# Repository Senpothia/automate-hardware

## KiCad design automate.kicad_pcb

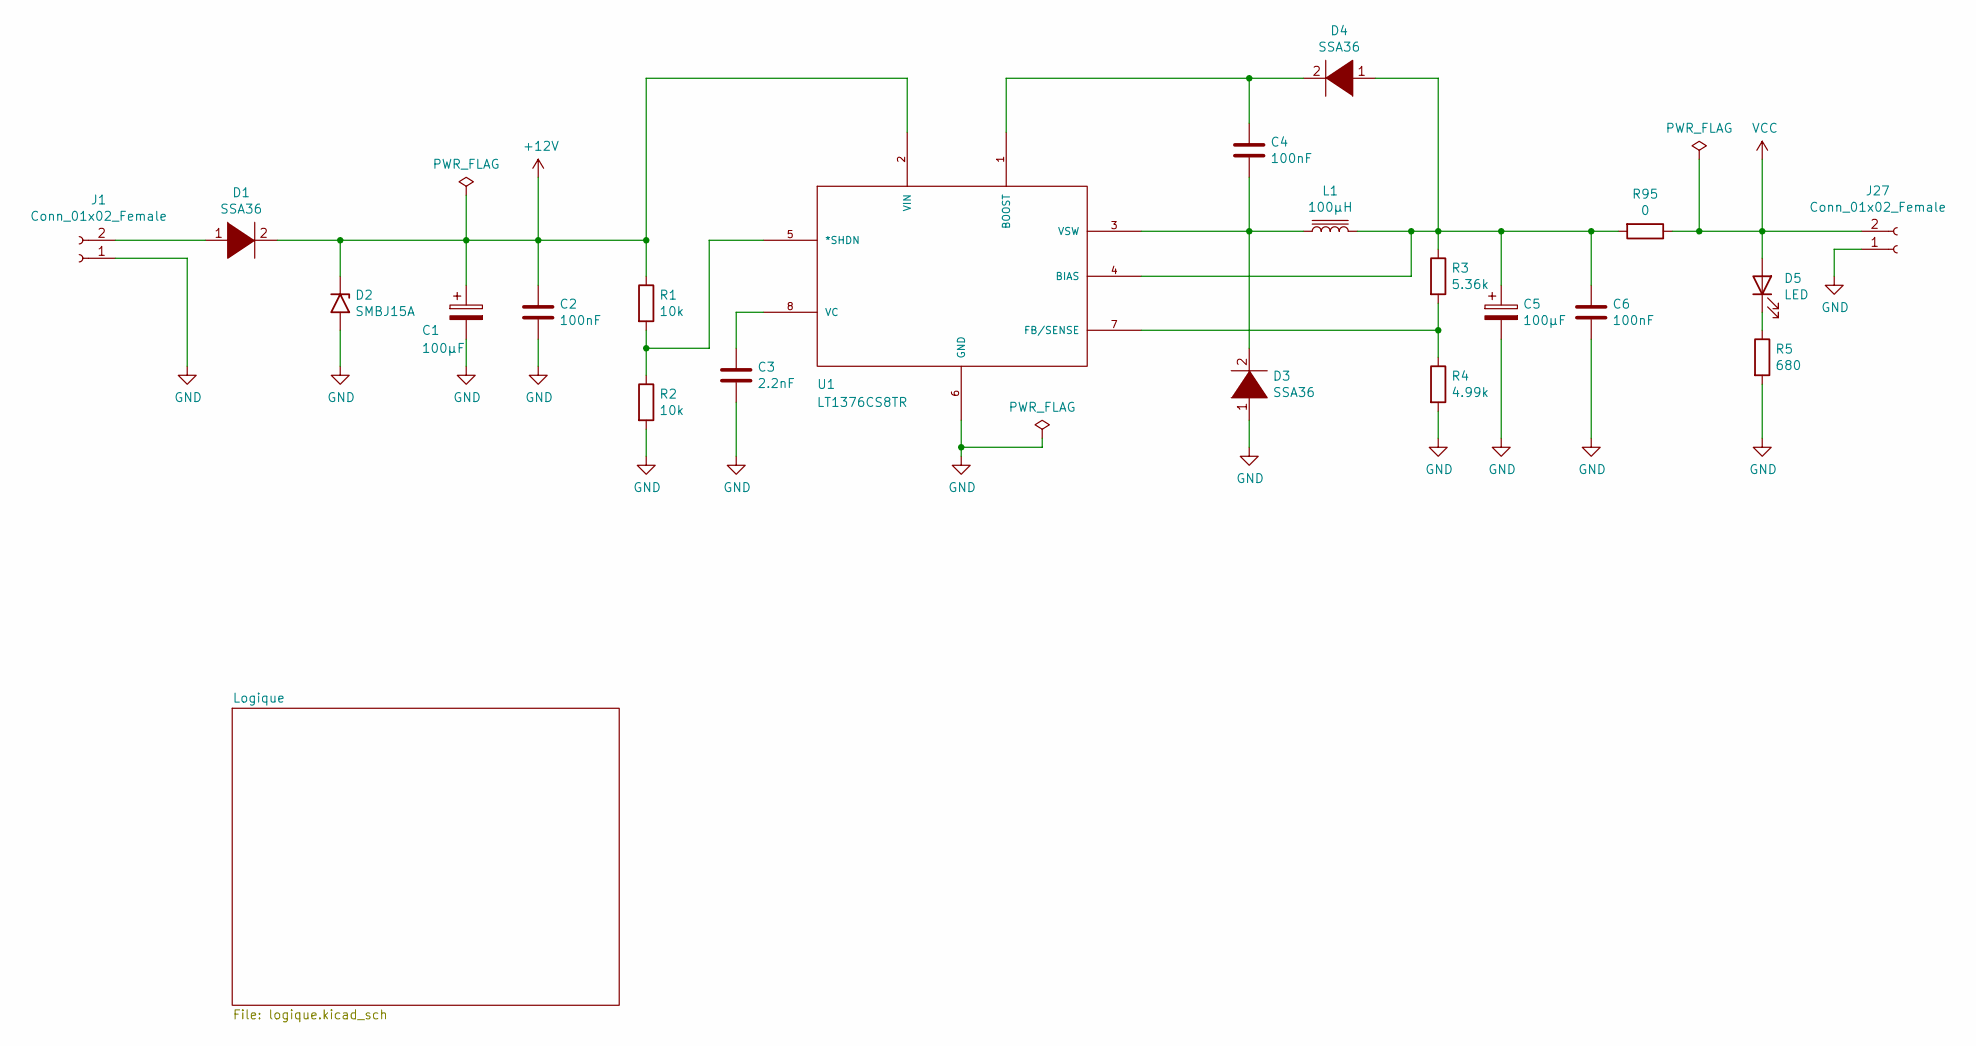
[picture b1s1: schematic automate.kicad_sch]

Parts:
C1, C5: 100µF; C_Elec_8x6.2
C2, C4, C6: 100nF; R_0805_2012Metric_Pad1.20x1.40mm_HandSolder
C3: 2.2nF; R_0805_2012Metric_Pad1.20x1.40mm_HandSolder
D1, D3, D4: SSA36; D_SMB_SSA36-Handsoldering
D2: SMBJ15A; D_SMB_Handsoldering
D5: LED; D_0805_2012Metric_Pad1.15x1.40mm_HandSolder
J1, J27: Conn_01x02_Female; conn-2pts-P5mm
L1: 100µH; L_Wuerth_WE-PD-Typ-LS-12x12
R1, R2: 10k; R_0805_2012Metric_Pad1.20x1.40mm_HandSolder
R3: 5.36k; R_0805_2012Metric_Pad1.20x1.40mm_HandSolder
R4: 4.99k; R_0805_2012Metric_Pad1.20x1.40mm_HandSolder
R5: 680; R_0805_2012Metric_Pad1.20x1.40mm_HandSolder
R95: 0; R_1206_3216Metric_Pad1.30x1.75mm_HandSolder
U1: LT1376CS8TR; SOIC-8_3.9x4.9mm_P1.27mm; MANUFACTURER_PART_NUMBER lt1376cs8#tr

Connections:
+12V: C1.1, C2.1, D1.2 (A), D2.1 (A1), R1.1, U1.2 (VIN); also elsewhere on the board
GND: C1.2, C2.2, C3.2, C5.2, C6.2, D2.2 (A2), D3.1 (K), J1.1, J27.1, R2.2, R4.2, R5.2, U1.6 (GND); also elsewhere on the board
unnamed: C3.1, U1.8 (VC)
unnamed: C4.1, D4.2 (A), U1.1 (BOOST)
unnamed: C4.2, D3.2 (A), L1.1, U1.3 (VSW)
unnamed: C5.1, C6.1, D4.1 (K), L1.2, R3.1, R95.2, U1.4 (BIAS)
unnamed: D1.1 (K), J1.2
unnamed: D5.1 (K), R5.1
unnamed: R1.2, R2.1, U1.5 (*SHDN)
unnamed: R3.2, R4.1, U1.7 (FB/SENSE)
VCC: D5.2 (A), J27.2, R95.1; also elsewhere on the board

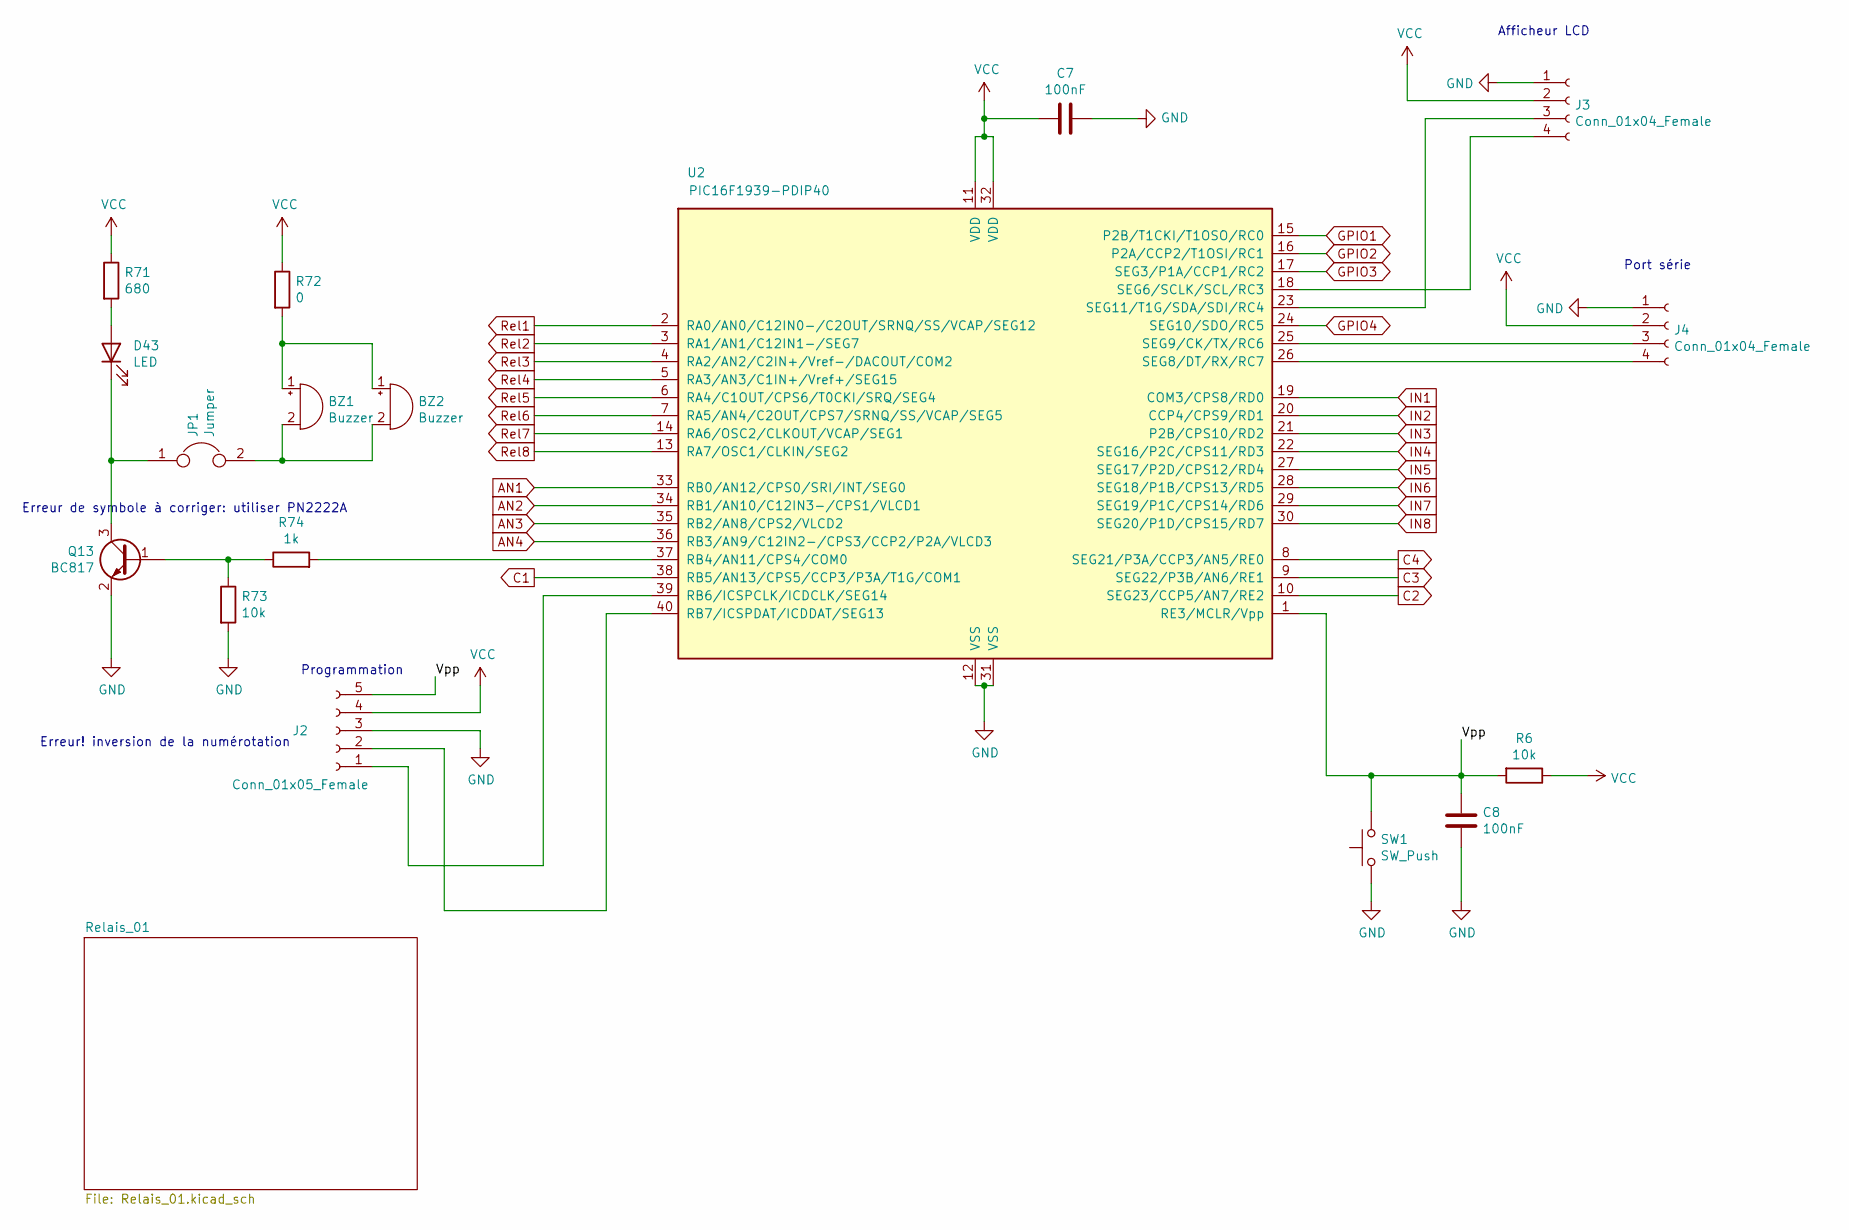
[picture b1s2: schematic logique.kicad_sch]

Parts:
BZ1: Buzzer; Buzzer_Mallory_AST1109MLTRQ
BZ2: Buzzer; Buzzer_12x9.5RM7.6
C7, C8: 100nF; R_0805_2012Metric_Pad1.20x1.40mm_HandSolder
D43: LED; LED_0805_2012Metric_Pad1.15x1.40mm_HandSolder
J2: Conn_01x05_Female; PinHeader_1x05_P2.54mm_Vertical
J3, J4: Conn_01x04_Female; conn-4pts-P5mm
JP1: Jumper; PinHeader_1x02_P2.54mm_Vertical
Q13: BC817; SOT-23.-BC817kicad_mod
R6, R73: 10k; R_0805_2012Metric_Pad1.20x1.40mm_HandSolder
R71: 680; R_0805_2012Metric_Pad1.20x1.40mm_HandSolder
R72: 0; R_0805_2012Metric_Pad1.20x1.40mm_HandSolder
R74: 1k; R_0805_2012Metric_Pad1.20x1.40mm_HandSolder
SW1: SW_Push; SW_PUSH_6mm_H5mm
U2: PIC16F1939-PDIP40; DIP-40_W15.24mm_LongPads

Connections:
/Logique/Vpp: C8.1, J2.5, R6.2, SW1.2, U2.1 (RE3/MCLR/Vpp)
AN1: U2.33 (RB0/AN12/CPS0/SRI/INT/SEG0); also elsewhere on the board
AN2: U2.34 (RB1/AN10/C12IN3-/CPS1/VLCD1); also elsewhere on the board
AN3: U2.35 (RB2/AN8/CPS2/VLCD2); also elsewhere on the board
AN4: U2.36 (RB3/AN9/C12IN2-/CPS3/CCP2/P2A/VLCD3); also elsewhere on the board
C1: U2.38 (RB5/AN13/CPS5/CCP3/P3A/T1G/COM1); also elsewhere on the board
C2: U2.10 (SEG23/CCP5/AN7/RE2); also elsewhere on the board
C3: U2.9 (SEG22/P3B/AN6/RE1); also elsewhere on the board
C4: U2.8 (SEG21/P3A/CCP3/AN5/RE0); also elsewhere on the board
GND: C7.1, C8.2, J2.3, J3.1, J4.1, Q13.2 (E), R73.2, SW1.1, U2.12 (VSS), U2.31 (VSS); also elsewhere on the board
GPIO1: U2.15 (P2B/T1CKI/T1OSO/RC0); also elsewhere on the board
GPIO2: U2.16 (P2A/CCP2/T1OSI/RC1); also elsewhere on the board
GPIO3: U2.17 (SEG3/P1A/CCP1/RC2); also elsewhere on the board
GPIO4: U2.24 (SEG10/SDO/RC5); also elsewhere on the board
IN1: U2.19 (COM3/CPS8/RD0); also elsewhere on the board
IN2: U2.20 (CCP4/CPS9/RD1); also elsewhere on the board
IN3: U2.21 (P2B/CPS10/RD2); also elsewhere on the board
IN4: U2.22 (SEG16/P2C/CPS11/RD3); also elsewhere on the board
IN5: U2.27 (SEG17/P2D/CPS12/RD4); also elsewhere on the board
IN6: U2.28 (SEG18/P1B/CPS13/RD5); also elsewhere on the board
IN7: U2.29 (SEG19/P1C/CPS14/RD6); also elsewhere on the board
IN8: U2.30 (SEG20/P1D/CPS15/RD7); also elsewhere on the board
unnamed: BZ1.1 (-), BZ2.1 (-), R72.2
unnamed: BZ1.2 (+), BZ2.2 (+), JP1.2
unnamed: D43.1 (K), JP1.1, Q13.3 (C)
unnamed: D43.2 (A), R71.2
unnamed: J2.1, U2.39 (RB6/ICSPCLK/ICDCLK/SEG14)
unnamed: J2.2, U2.40 (RB7/ICSPDAT/ICDDAT/SEG13)
unnamed: J3.3, U2.23 (SEG11/T1G/SDA/SDI/RC4)
unnamed: J3.4, U2.18 (SEG6/SCLK/SCL/RC3)
unnamed: J4.3, U2.25 (SEG9/CK/TX/RC6)
unnamed: J4.4, U2.26 (SEG8/DT/RX/RC7)
unnamed: Q13.1 (B), R73.1, R74.1
unnamed: R74.2, U2.37 (RB4/AN11/CPS4/COM0)
Rel1: U2.2 (RA0/AN0/C12IN0-/C2OUT/SRNQ/SS/VCAP/SEG12); also elsewhere on the board
Rel2: U2.3 (RA1/AN1/C12IN1-/SEG7); also elsewhere on the board
Rel3: U2.4 (RA2/AN2/C2IN+/Vref-/DACOUT/COM2); also elsewhere on the board
Rel4: U2.5 (RA3/AN3/C1IN+/Vref+/SEG15); also elsewhere on the board
Rel5: U2.6 (RA4/C1OUT/CPS6/T0CKI/SRQ/SEG4); also elsewhere on the board
Rel6: U2.7 (RA5/AN4/C2OUT/CPS7/SRNQ/SS/VCAP/SEG5); also elsewhere on the board
Rel7: U2.14 (RA6/OSC2/CLKOUT/VCAP/SEG1); also elsewhere on the board
Rel8: U2.13 (RA7/OSC1/CLKIN/SEG2); also elsewhere on the board
VCC: C7.2, J2.4, J3.2, J4.2, R6.1, R71.1, R72.1, U2.11 (VDD), U2.32 (VDD); also elsewhere on the board

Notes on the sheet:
Erreur! inversion de la numérotation
Afficheur LCD
Port série
Programmation
Erreur de symbole à corriger: utiliser PN2222A

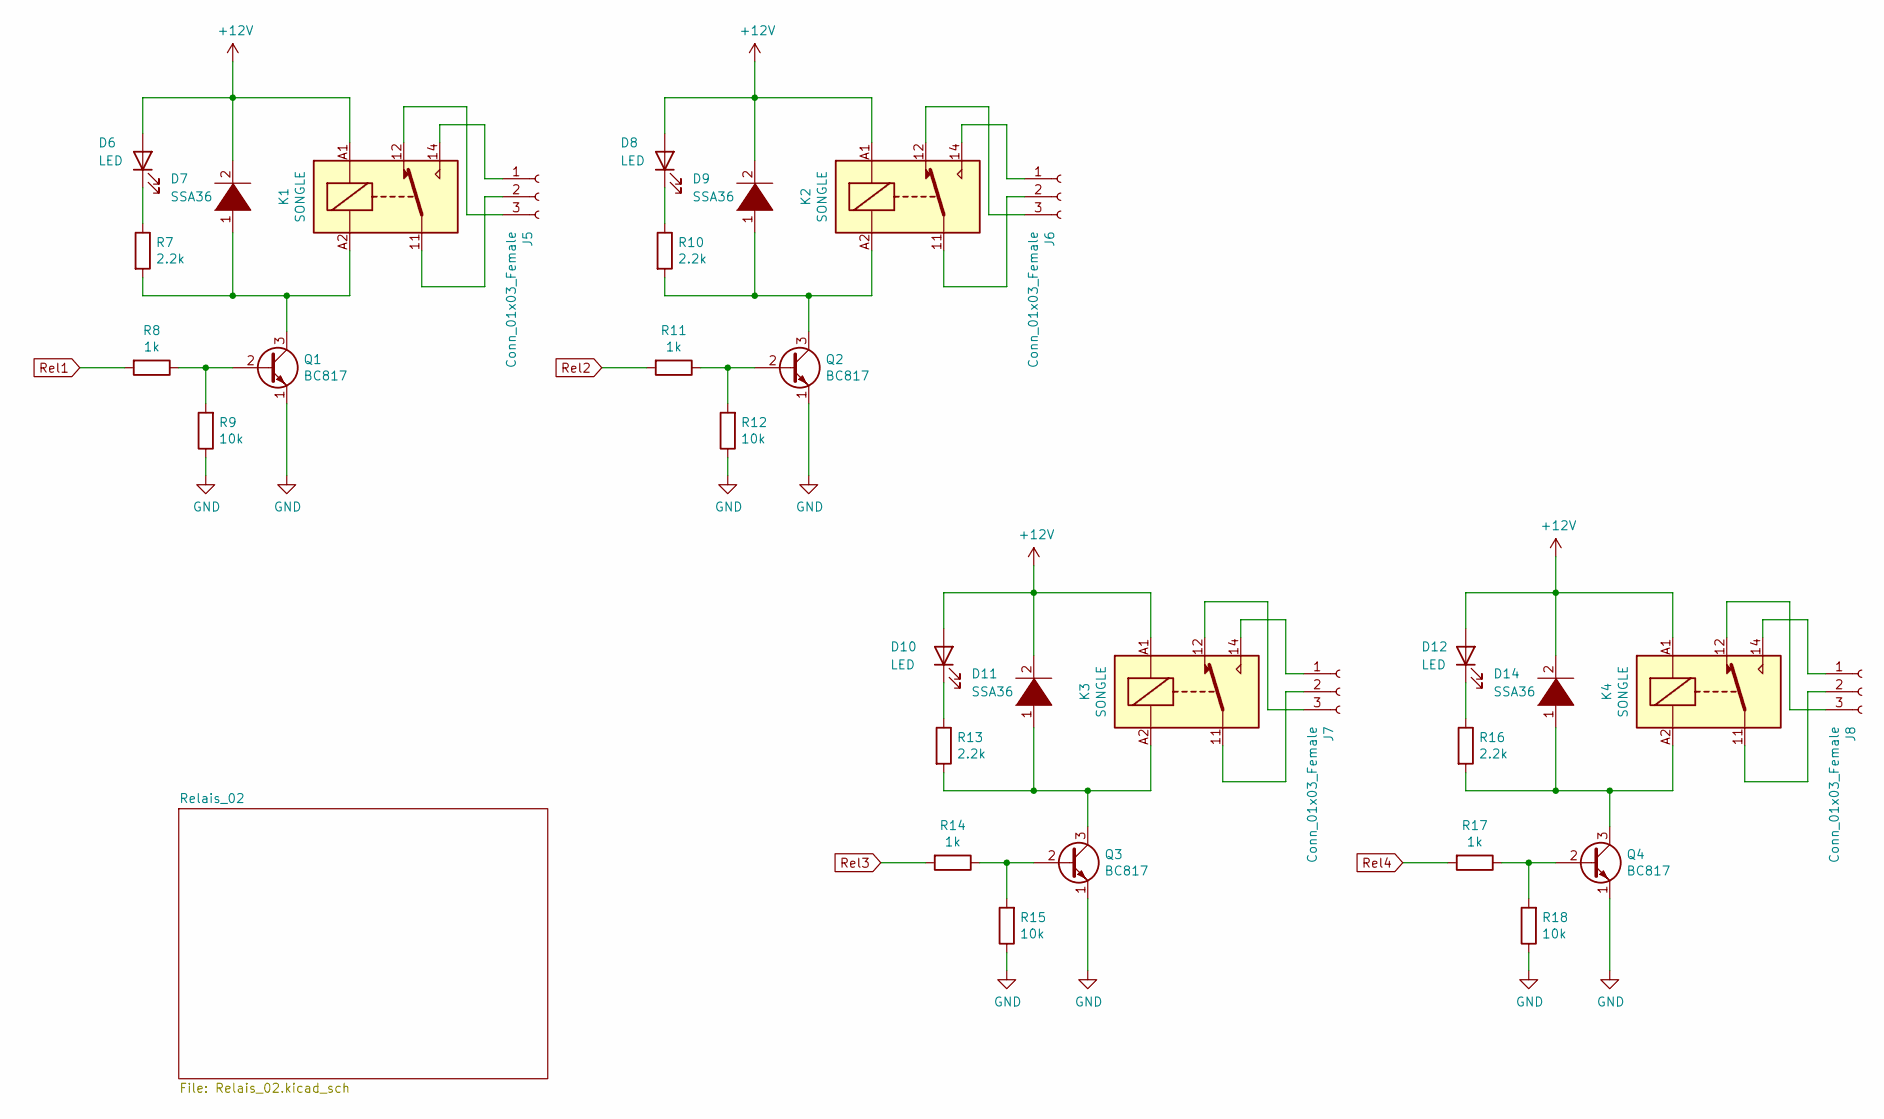
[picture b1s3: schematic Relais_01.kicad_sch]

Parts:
D6, D8, D10, D12: LED; D_0805_2012Metric_Pad1.15x1.40mm_HandSolder
D7, D9, D11: SSA36; D_SMB_SSA36-Handsoldering
D14: SSA36; D_SMB_Handsoldering
J5, J6, J7, J8: Conn_01x03_Female; conn-3pts-P5mm
K1, K2, K3, K4: SONGLE; Relay_SRD_Series_Form_C
Q1, Q2, Q3, Q4: BC817; SOT-23.-BC817kicad_mod
R7, R10, R13, R16: 2.2k; R_0805_2012Metric_Pad1.20x1.40mm_HandSolder
R8, R11, R14, R17: 1k; R_0805_2012Metric_Pad1.20x1.40mm_HandSolder
R9, R12, R15, R18: 10k; R_0805_2012Metric_Pad1.20x1.40mm_HandSolder

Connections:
+12V: D6.2 (A), D7.2 (A), D8.2 (A), D9.2 (A), D10.2 (A), D11.2 (A), D12.2 (A), D14.2 (A), K1.A1, K2.A1, K3.A1, K4.A1; also elsewhere on the board
GND: Q1.1 (E), Q2.1 (E), Q3.1 (E), Q4.1 (E), R9.1, R12.1, R15.1, R18.1; also elsewhere on the board
unnamed: D6.1 (K), R7.1
unnamed: D7.1 (K), K1.A2, Q1.3 (C), R7.2
unnamed: D8.1 (K), R10.1
unnamed: D9.1 (K), K2.A2, Q2.3 (C), R10.2
unnamed: D10.1 (K), R13.1
unnamed: D11.1 (K), K3.A2, Q3.3 (C), R13.2
unnamed: D12.1 (K), R16.1
unnamed: D14.1 (K), K4.A2, Q4.3 (C), R16.2
unnamed: J5.1, K1.14
unnamed: J5.2, K1.11
unnamed: J5.3, K1.12
unnamed: J6.1, K2.14
unnamed: J6.2, K2.11
unnamed: J6.3, K2.12
unnamed: J7.1, K3.14
unnamed: J7.2, K3.11
unnamed: J7.3, K3.12
unnamed: J8.1, K4.14
unnamed: J8.2, K4.11
unnamed: J8.3, K4.12
unnamed: Q1.2 (B), R8.1, R9.2
unnamed: Q2.2 (B), R11.1, R12.2
unnamed: Q3.2 (B), R14.1, R15.2
unnamed: Q4.2 (B), R17.1, R18.2
Rel1: R8.2; also elsewhere on the board
Rel2: R11.2; also elsewhere on the board
Rel3: R14.2; also elsewhere on the board
Rel4: R17.2; also elsewhere on the board

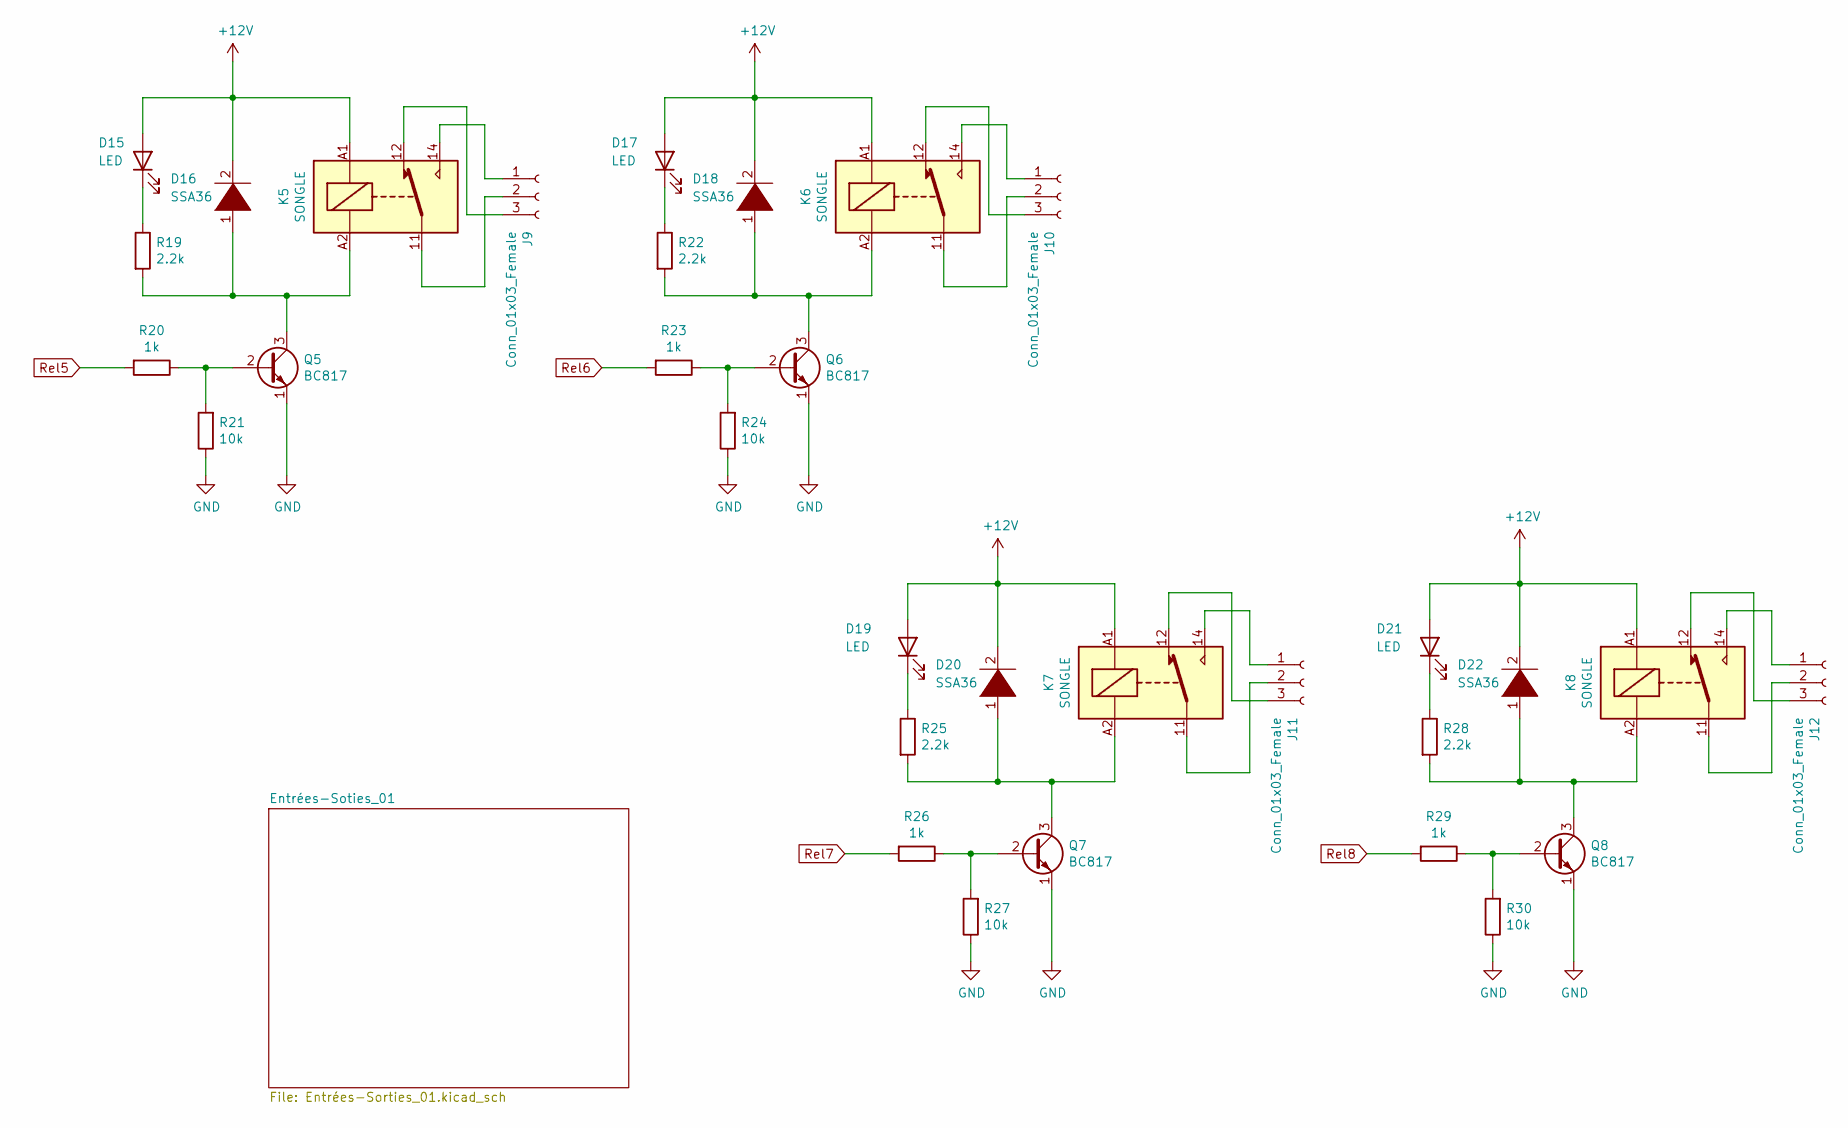
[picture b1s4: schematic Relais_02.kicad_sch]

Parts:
D15, D17, D19, D21: LED; D_0805_2012Metric_Pad1.15x1.40mm_HandSolder
D16, D18, D20, D22: SSA36; D_SMB_SSA36-Handsoldering
J9, J10, J11, J12: Conn_01x03_Female; conn-3pts-P5mm
K5, K6, K7, K8: SONGLE; Relay_SRD_Series_Form_C
Q5, Q6, Q7, Q8: BC817; SOT-23.-BC817kicad_mod
R19, R22, R25, R28: 2.2k; R_0805_2012Metric_Pad1.20x1.40mm_HandSolder
R20, R23, R26, R29: 1k; R_0805_2012Metric_Pad1.20x1.40mm_HandSolder
R21, R24, R27, R30: 10k; R_0805_2012Metric_Pad1.20x1.40mm_HandSolder

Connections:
+12V: D15.2 (A), D16.2 (A), D17.2 (A), D18.2 (A), D19.2 (A), D20.2 (A), D21.2 (A), D22.2 (A), K5.A1, K6.A1, K7.A1, K8.A1; also elsewhere on the board
GND: Q5.1 (E), Q6.1 (E), Q7.1 (E), Q8.1 (E), R21.1, R24.1, R27.1, R30.1; also elsewhere on the board
unnamed: D15.1 (K), R19.1
unnamed: D16.1 (K), K5.A2, Q5.3 (C), R19.2
unnamed: D17.1 (K), R22.1
unnamed: D18.1 (K), K6.A2, Q6.3 (C), R22.2
unnamed: D19.1 (K), R25.1
unnamed: D20.1 (K), K7.A2, Q7.3 (C), R25.2
unnamed: D21.1 (K), R28.1
unnamed: D22.1 (K), K8.A2, Q8.3 (C), R28.2
unnamed: J9.1, K5.14
unnamed: J9.2, K5.11
unnamed: J9.3, K5.12
unnamed: J10.1, K6.14
unnamed: J10.2, K6.11
unnamed: J10.3, K6.12
unnamed: J11.1, K7.14
unnamed: J11.2, K7.11
unnamed: J11.3, K7.12
unnamed: J12.1, K8.14
unnamed: J12.2, K8.11
unnamed: J12.3, K8.12
unnamed: Q5.2 (B), R20.1, R21.2
unnamed: Q6.2 (B), R23.1, R24.2
unnamed: Q7.2 (B), R26.1, R27.2
unnamed: Q8.2 (B), R29.1, R30.2
Rel5: R20.2; also elsewhere on the board
Rel6: R23.2; also elsewhere on the board
Rel7: R26.2; also elsewhere on the board
Rel8: R29.2; also elsewhere on the board

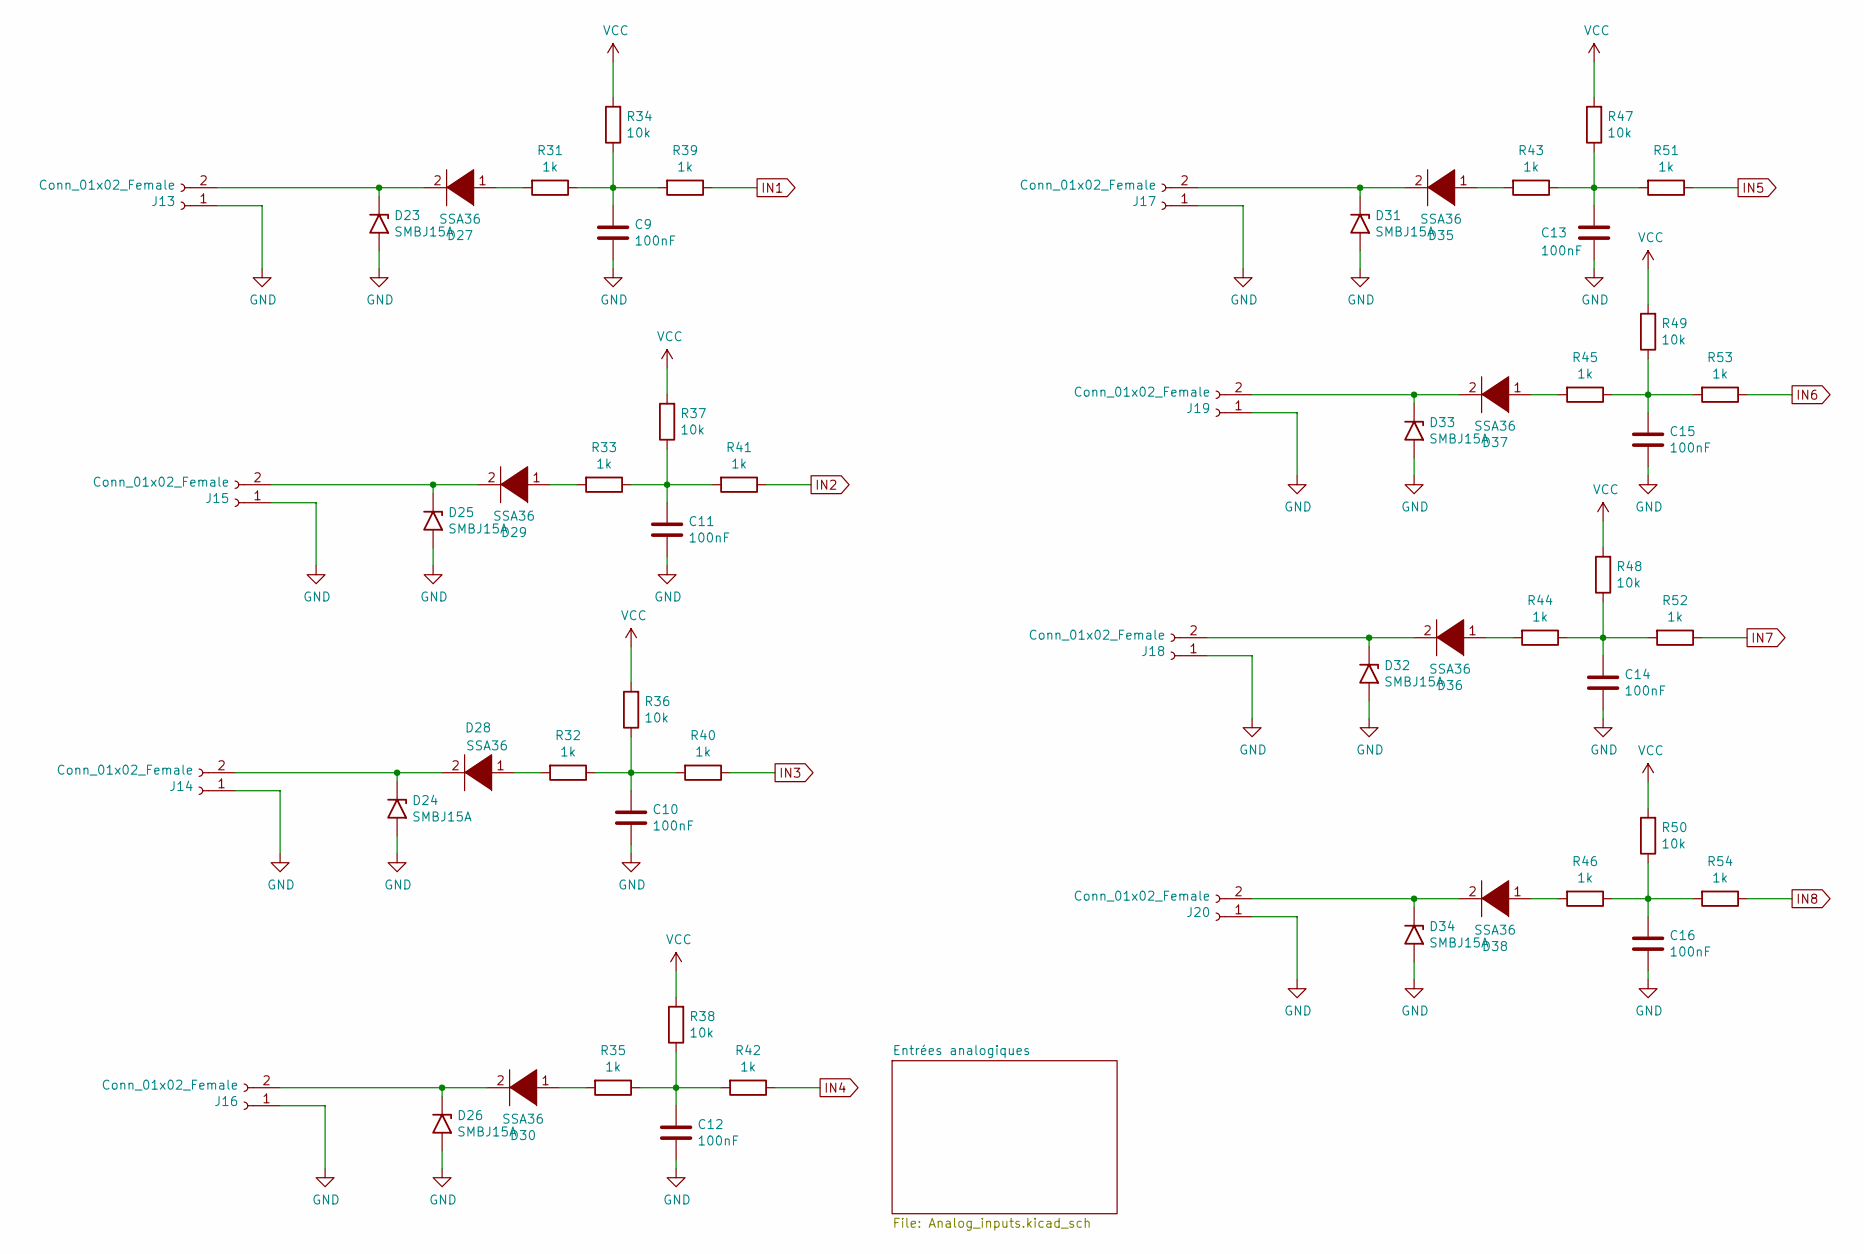
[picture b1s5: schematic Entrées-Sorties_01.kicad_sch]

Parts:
C9, C10, C11, C12, C13, C14, C15, C16: 100nF; R_0805_2012Metric_Pad1.20x1.40mm_HandSolder
D23, D24, D25, D26, D31, D32, D33, D34: SMBJ15A; D_SMB_Handsoldering
D27, D28, D29, D30, D35, D36, D37, D38: SSA36; D_SMB_SSA36-Handsoldering
J13, J14, J15, J16, J17, J18, J19, J20: Conn_01x02_Female; conn-2pts-P5mm
R31, R32, R33, R35, R39, R40, R41, R42, R43, R44, R45, R46, R51, R52, R53, R54: 1k; R_0805_2012Metric_Pad1.20x1.40mm_HandSolder
R34, R36, R37, R38, R47, R48, R49, R50: 10k; R_0805_2012Metric_Pad1.20x1.40mm_HandSolder

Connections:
GND: C9.2, C10.2, C11.2, C12.2, C13.2, C14.2, C15.2, C16.2, D23.2 (A2), D24.2 (A2), D25.2 (A2), D26.2 (A2), D31.2 (A2), D32.2 (A2), D33.2 (A2), D34.2 (A2), J13.1, J14.1, J15.1, J16.1, J17.1, J18.1, J19.1, J20.1; also elsewhere on the board
IN1: R39.1; also elsewhere on the board
IN2: R41.1; also elsewhere on the board
IN3: R40.1; also elsewhere on the board
IN4: R42.1; also elsewhere on the board
IN5: R51.1; also elsewhere on the board
IN6: R53.1; also elsewhere on the board
IN7: R52.1; also elsewhere on the board
IN8: R54.1; also elsewhere on the board
unnamed: C9.1, R31.1, R34.1, R39.2
unnamed: C10.1, R32.1, R36.1, R40.2
unnamed: C11.1, R33.1, R37.1, R41.2
unnamed: C12.1, R35.1, R38.1, R42.2
unnamed: C13.1, R43.1, R47.1, R51.2
unnamed: C14.1, R44.1, R48.1, R52.2
unnamed: C15.1, R45.1, R49.1, R53.2
unnamed: C16.1, R46.1, R50.1, R54.2
unnamed: D23.1 (A1), D27.2 (A), J13.2
unnamed: D24.1 (A1), D28.2 (A), J14.2
unnamed: D25.1 (A1), D29.2 (A), J15.2
unnamed: D26.1 (A1), D30.2 (A), J16.2
unnamed: D27.1 (K), R31.2
unnamed: D28.1 (K), R32.2
unnamed: D29.1 (K), R33.2
unnamed: D30.1 (K), R35.2
unnamed: D31.1 (A1), D35.2 (A), J17.2
unnamed: D32.1 (A1), D36.2 (A), J18.2
unnamed: D33.1 (A1), D37.2 (A), J19.2
unnamed: D34.1 (A1), D38.2 (A), J20.2
unnamed: D35.1 (K), R43.2
unnamed: D36.1 (K), R44.2
unnamed: D37.1 (K), R45.2
unnamed: D38.1 (K), R46.2
VCC: R34.2, R36.2, R37.2, R38.2, R47.2, R48.2, R49.2, R50.2; also elsewhere on the board

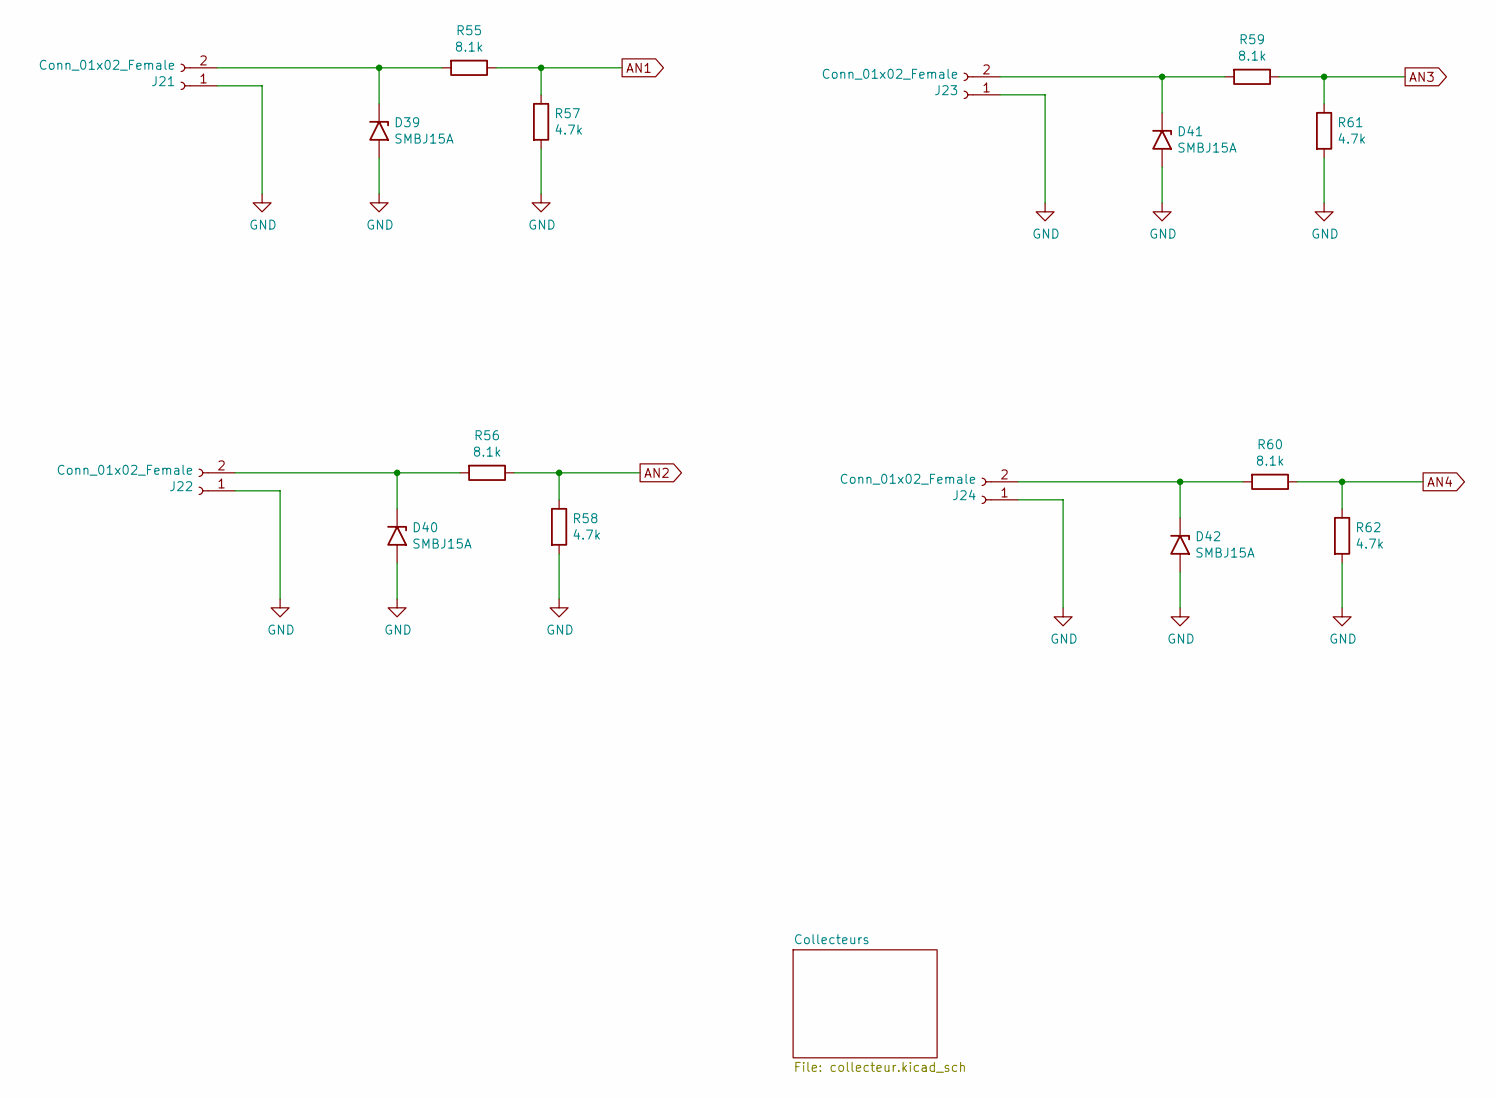
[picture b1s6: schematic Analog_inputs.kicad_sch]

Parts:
D39, D40, D41, D42: SMBJ15A; D_SMB_Handsoldering
J21, J22, J23, J24: Conn_01x02_Female; conn-2pts-P5mm
R55, R56, R59, R60: 8.1k; R_0805_2012Metric_Pad1.20x1.40mm_HandSolder
R57, R58, R61, R62: 4.7k; R_0805_2012Metric_Pad1.20x1.40mm_HandSolder

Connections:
AN1: R55.1, R57.1; also elsewhere on the board
AN2: R56.1, R58.1; also elsewhere on the board
AN3: R59.1, R61.1; also elsewhere on the board
AN4: R60.1, R62.1; also elsewhere on the board
GND: D39.2 (A2), D40.2 (A2), D41.2 (A2), D42.2 (A2), J21.1, J22.1, J23.1, J24.1, R57.2, R58.2, R61.2, R62.2; also elsewhere on the board
unnamed: D39.1 (A1), J21.2, R55.2
unnamed: D40.1 (A1), J22.2, R56.2
unnamed: D41.1 (A1), J23.2, R59.2
unnamed: D42.1 (A1), J24.2, R60.2

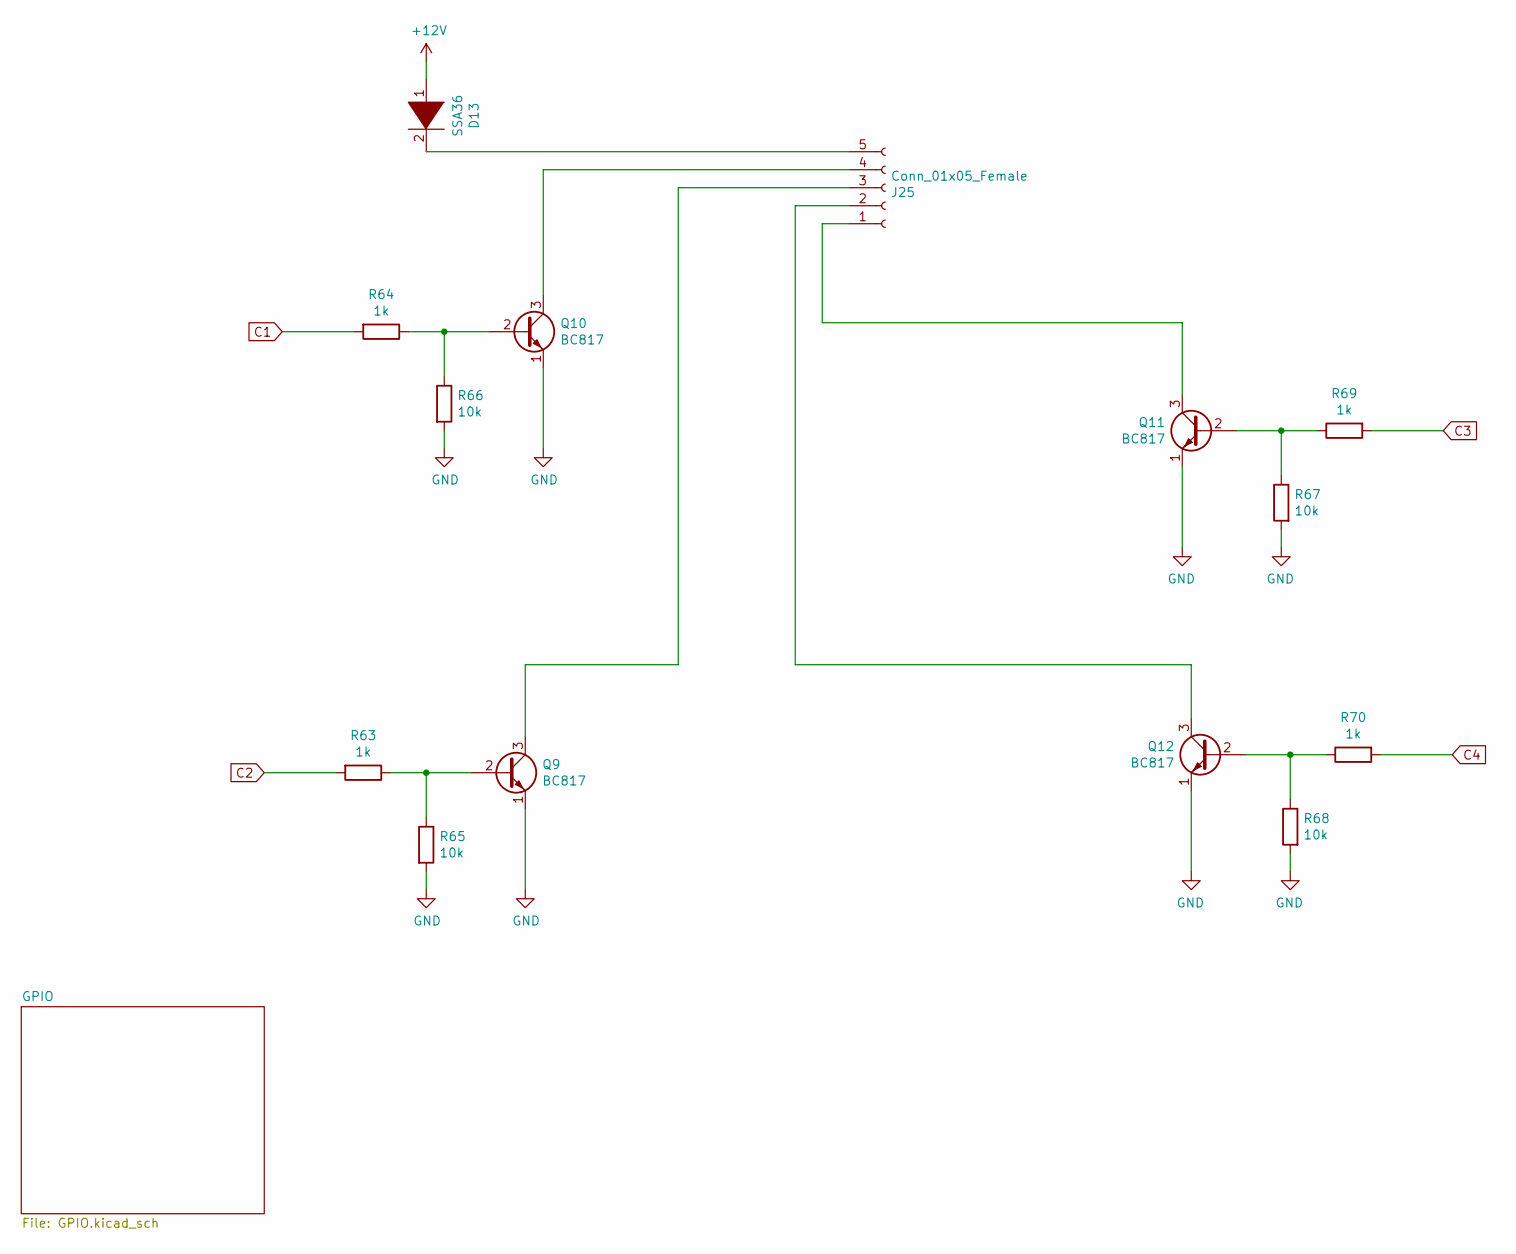
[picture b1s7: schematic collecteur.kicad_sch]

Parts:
D13: SSA36; D_SMB_SSA36-Handsoldering
J25: Conn_01x05_Female; conn-5pts-P5mm
Q9, Q10, Q11, Q12: BC817; SOT-23.-BC817kicad_mod
R63, R64, R69, R70: 1k; R_0805_2012Metric_Pad1.20x1.40mm_HandSolder
R65, R66, R67, R68: 10k; R_0805_2012Metric_Pad1.20x1.40mm_HandSolder

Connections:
+12V: D13.1 (K); also elsewhere on the board
C1: R64.2; also elsewhere on the board
C2: R63.2; also elsewhere on the board
C3: R69.2; also elsewhere on the board
C4: R70.2; also elsewhere on the board
GND: Q9.1 (E), Q10.1 (E), Q11.1 (E), Q12.1 (E), R65.2, R66.2, R67.2, R68.2; also elsewhere on the board
unnamed: D13.2 (A), J25.5
unnamed: J25.1, Q11.3 (C)
unnamed: J25.2, Q12.3 (C)
unnamed: J25.3, Q9.3 (C)
unnamed: J25.4, Q10.3 (C)
unnamed: Q9.2 (B), R63.1, R65.1
unnamed: Q10.2 (B), R64.1, R66.1
unnamed: Q11.2 (B), R67.1, R69.1
unnamed: Q12.2 (B), R68.1, R70.1
